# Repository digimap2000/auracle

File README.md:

# Auracle

Professional desktop test harness for Auracast LE Audio broadcast streams.

Built with a C++ backend (CMake) and a Tauri 2 / React 18 frontend.

## Repository layout

```
proto/          Protocol Buffer definitions
backend/        C++ daemon, inventory library, gRPC service, CLI
frontend/       Tauri 2 + React 18 desktop UI
src-tauri/      Tauri Rust shell (bridges frontend ↔ backend)
docs/           Specifications and architecture docs
```

## Building

See [docs/build.md](docs/build.md) for full build instructions.

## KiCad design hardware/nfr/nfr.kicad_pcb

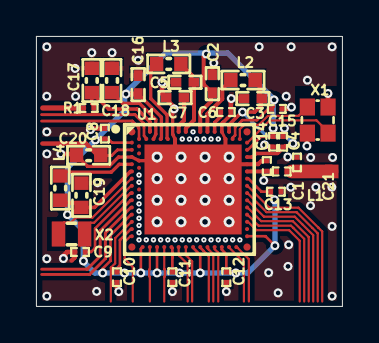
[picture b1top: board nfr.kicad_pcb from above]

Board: 4 copper layers, 17.0 x 15.0 mm, 29 parts (0 on the bottom side), 18 nets.

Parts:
C1: 0.7pF; CAPC0603X03L_C
C2, C3, C5, C7, C16: 1.0µF; CAPC1005X04L
C4: 2.2nF; CAPC0603X03L_C
C6, C8, C9, C10, C11, C12, C13, C14, C15: 100nF; CAPC0603X03L_C
C17, C18, C20: 4.7µF; CAPC1608X06L
C19: 2.2µF; CAPC1608X06L
C21: N.C.; CAPC0603X03L_C_NC
L1: 2.2nH; INDC0603X03L_C
L2, L3, L4: 10µH; INDC1608X06L
R1: 2R2; RESC0603X03L_C
U1: nRF5340-QKAA; AQFN40P700X700X85_HS-99N
X1: 32MHz; BT-XTAL_2016
X2: 32.768kHz; XTAL_2012

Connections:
ANT: C1.2, L1.2, U1.L31
GND: C1.1, C2.2, C3.1, C4.2, C5.1, C6.2, C7.1, C8.2, C9.2, C10.2, C11.2, C12.2, C13.2, C14.2, C15.2, C16.1, C17.2, C18.2, C19.2, C20.2, C21.1, U1.104, U1.A25, U1.B12, U1.B26, U1.G1, U1.H2, U1.J31, X1.2, X1.4
NetC3_2: C3.2, C4.1, L2.1, U1.A27, U1.G31
NetC5_2: C5.2, L3.1, U1.A15
NetC6_1: C6.1, U1.A23
NetC7_2: C7.2, U1.A13
NetC17_1: C17.1, R1.2, U1.A5
NetC18_1: C18.1, U1.B6
NetL2_2: L2.2, U1.A21
NetL3_2: L3.2, U1.B10
NetL4_1: L4.1, U1.J1
P0.00/XL1: U1.N1, X2.1
P0.01/XL2: U1.R1, X2.2
RF: C21.2, L1.1
VDD_HV: C20.1, U1.E1
VDD_NRF: C2.1, C8.1, C9.1, C10.1, C11.1, C12.1, C13.1, C14.1, C15.1, C16.2, C19.1, L4.2, U1.A19, U1.AC1, U1.AG1, U1.AJ31, U1.AL3, U1.AL7, U1.AL11, U1.AL17, U1.AL25, U1.B8, U1.B28, U1.C1, U1.E31, U1.L1, U1.N31, U1.U1
XC1: U1.C31, X1.1
XC2: U1.B30, X1.3

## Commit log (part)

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2026-03-09 Implement ESP32 bridge protocol and nRF scan tap
2026-03-09 Add ESP32 discovery cache and API
2026-03-09 Pivot ESP32 app to raw TCP UART bridge
2026-03-09 Add nRF runtime modes for monitor and sink
2026-03-10 Sync up the loose ends.
2026-03-11 Implement multi-unit scan diagnostics flow
2026-03-11 Polish BLE scan diagnostics UI
2026-03-11 Make unit selection local to scan views
2026-03-11 Refine scan device detail workspace
2026-03-11 Add daemon-backed BLE payload decoding
2026-03-11 Move BLE service decode formats to YAML
2026-03-11 Add service format implications metadata
2026-03-11 Add compliance DSL and evaluator
2026-03-11 Add compliance rule loading and normalization
2026-03-11 Add daemon-backed compliance execution flow
2026-03-11 Refine compliance DSL and target single DUTs
